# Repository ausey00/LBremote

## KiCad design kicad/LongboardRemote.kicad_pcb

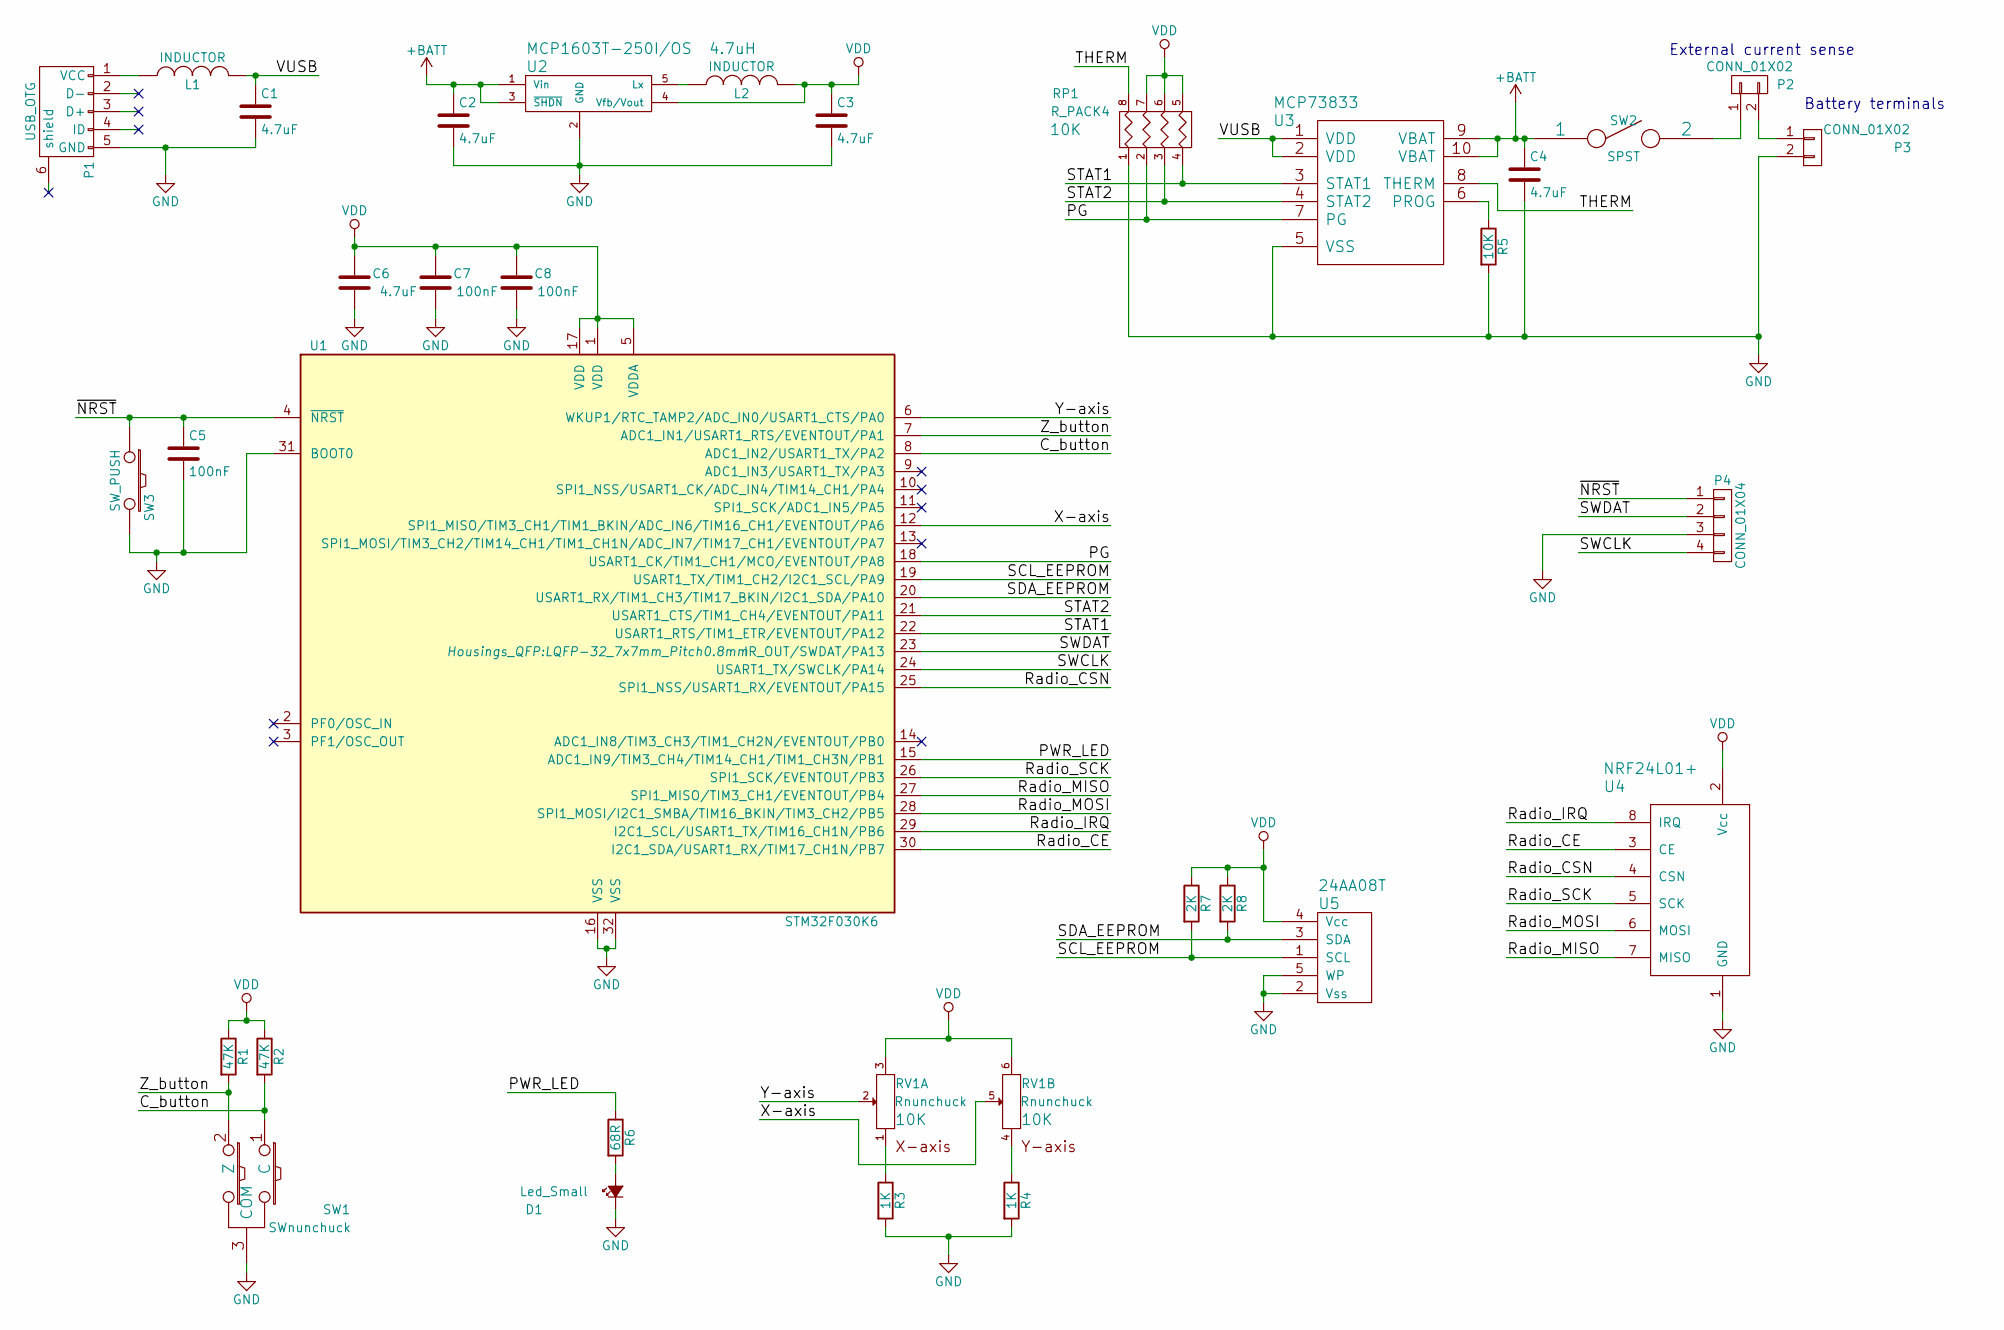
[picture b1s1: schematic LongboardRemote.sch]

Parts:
C1, C2, C3, C4, C6: 4.7uF; C_0805_HandSoldering
C5, C7, C8: 100nF; C_0805_HandSoldering
D1: Led_Small; C_0805_HandSoldering
L1: INDUCTOR; C_0805_HandSoldering
L2: INDUCTOR; TantalC_SizeR_EIA-2012
P1: USB_OTG; USB_Mini-B
P2, P3: CONN_01X02; Pin_Header_Straight_1x02
P4: CONN_01X04; Socket_Strip_Straight_1x04
R1, R2: 47K; R_0805_HandSoldering
R3, R4: 1K; R_0805_HandSoldering
R5: 10K; R_0805_HandSoldering
R6: 68R; R_0805_HandSoldering
R7, R8: 2K; R_0805_HandSoldering
RP1: R_PACK4; R_Array_Concave_4x0603
RV1: Rnunchuck
SW1: SWnunchuck; SW_Micro_SPST
SW2: SPST; Pin_Header_Straight_1x03
SW3: SW_PUSH; SW_SMD_TACT_5.15x4.6
U1: STM32F030K6; LQFP-32_7x7mm_Pitch0.8mm
U2: MCP1603T-250I/OS; SOT-23-5
U3: MCP73833; MSOP-10_3x3mm_Pitch0.5mm
U4: NRF24L01+; Pin_Header_Straight_2x04
U5: 24AA08T; SOT-23-5

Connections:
+BATT: C2.1, C4.1, SW2.1, U2.1 (Vin), U2.3 (~SHDN), U3.9 (VBAT), U3.10 (VBAT)
/C_button: R2.2, SW1.1 (C), U1.8 (ADC1_IN2/USART1_TX/PA2)
/PG: RP1.2, U1.18 (USART1_CK/TIM1_CH1/MCO/EVENTOUT/PA8), U3.7 (PG)
/PWR_LED: R6.1, U1.15 (ADC1_IN9/TIM3_CH4/TIM14_CH1/TIM1_CH3N/P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)
/Radio_CE: U1.30 (I2C1_SDA/USART1_RX/TIM17_CH1N/PB7), U4.3 (CE)
/Radio_CSN: U1.25 (SPI1_NSS/USART1_RX/EVENTOUT/PA15), U4.4 (CSN)
/Radio_IRQ: U1.29 (I2C1_SCL/USART1_TX/TIM16_CH1N/PB6), U4.8 (IRQ)
/Radio_MISO: U1.27 (SPI1_MISO/TIM3_CH1/EVENTOUT/PB4), U4.7 (MISO)
/Radio_MOSI: U1.28 (SPI1_MOSI/I2C1_SMBA/TIM16_BKIN/TIM3_CH2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), U4.6 (MOSI)
/Radio_SCK: U1.26 (SPI1_SCK/EVENTOUT/PB3), U4.5 (SCK)
/SCL_EEPROM: R7.2, U1.19 (USART1_TX/TIM1_CH2/I2C1_SCL/PA9), U5.1 (SCL)
/SDA_EEPROM: R8.2, U1.20 (USART1_RX/TIM1_CH3/TIM17_BKIN/I2C1_SDA/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), U5.3 (SDA)
/STAT1: RP1.4, U1.22 (USART1_RTS/TIM1_ETR/EVENTOUT/PA12), U3.3 (STAT1)
/STAT2: RP1.3, U1.21 (USART1_CTS/TIM1_CH4/EVENTOUT/PA11), U3.4 (STAT2)
/SWCLK: P4.4, U1.24 (USART1_TX/SWCLK/PA14)
/SWDAT: P4.2, U1.23 (IR_OUT/SWDAT/PA13)
/THERM: RP1.8 (R1), U3.8 (THERM)
/VUSB: C1.1, L1.2, U3.1 (VDD), U3.2 (VDD)
/X-axis: RV1.5, U1.12 (SPI1_MISO/TIM3_CH1/TIM1_BKIN/ADC_IN6/TI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)
/Y-axis: RV1.2 (5), U1.6 (WKUP1/RTC_TAMP2/ADC_IN0/USART1_CTS/PA0)
/Z_button: R1.2, SW1.2 (Z), U1.7 (ADC1_IN1/USART1_RTS/EVENTOUT/PA1)
/~NRST: C5.1, P4.1, SW3.1, U1.4 (~NRST)
GND: C1.2, C2.2, C3.2, C4.2, C5.2, C6.1, C7.1, C8.1, D1.1 (K), P1.5 (GND), P3.2, P4.3, R3.2, R4.2, R5.2, RP1.1, SW1.3 (COM), SW3.2, U1.16 (VSS), U1.31 (BOOT0), U1.32 (VSS), U2.2 (GND), U3.5 (VSS), U4.1 (GND), U5.2 (Vss), U5.5 (WP)
unnamed: D1.2 (A), R6.2
unnamed: L1.1, P1.1 (VCC)
unnamed: L2.1, U2.5 (Lx)
unnamed: P2.1, SW2.2
unnamed: P2.2, P3.1
unnamed: R3.1, RV1.1 (4)
unnamed: R4.1, RV1.4
unnamed: R5.1, U3.6 (PROG)
VDD: C3.1, C6.2, C7.2, C8.2, L2.2, R1.1, R2.1, R7.1, R8.1, RP1.5 (R4), RP1.6 (R3), RP1.7 (R2), RV1.3 (6), RV1.6, U1.1 (VDD), U1.5 (VDDA), U1.17 (VDD), U2.4 (Vfb/Vout), U4.2 (Vcc), U5.4 (Vcc)

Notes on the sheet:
External current sense
Battery terminals

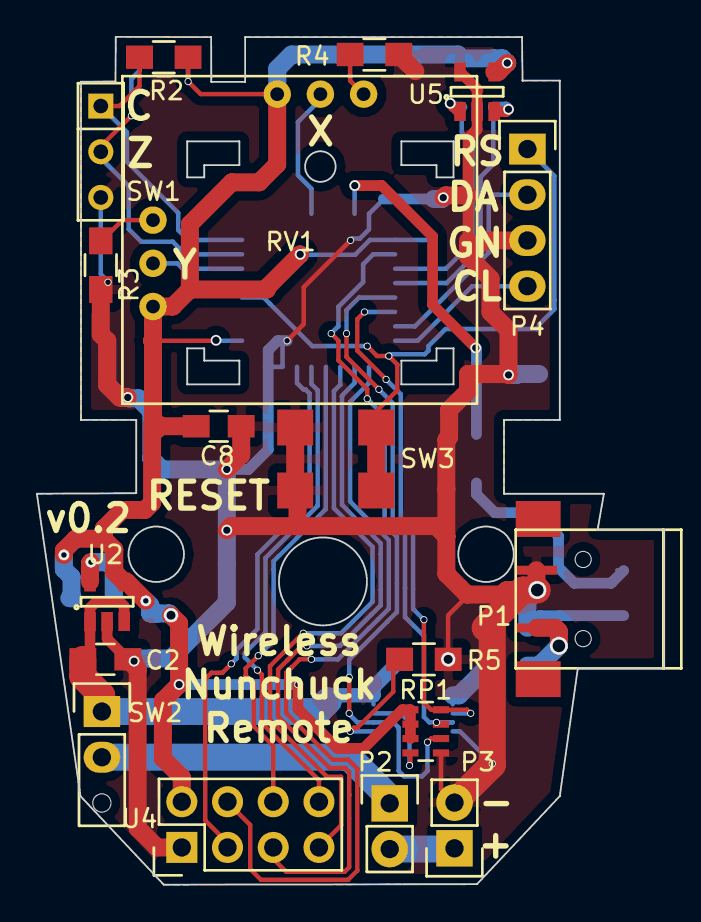
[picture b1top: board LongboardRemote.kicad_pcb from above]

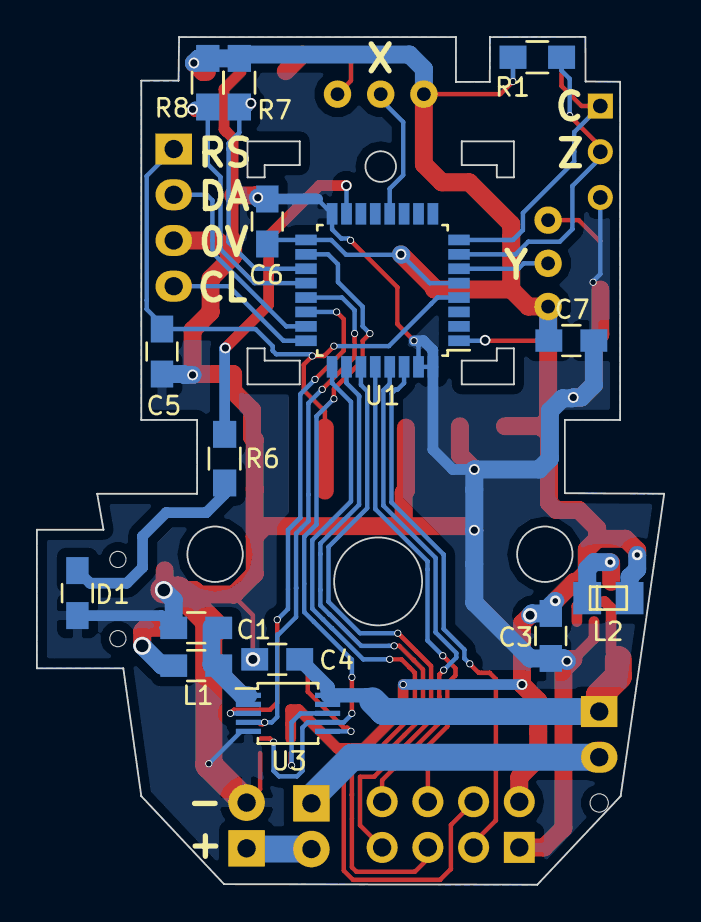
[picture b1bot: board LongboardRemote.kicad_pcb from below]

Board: 2 copper layers, 34.9 x 47.1 mm, 33 parts (15 on the bottom side), 32 nets.

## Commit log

2015-06-11 added changelog with v0.3 updates
